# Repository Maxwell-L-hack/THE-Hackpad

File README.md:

# THE-hackpad
This macropad is a six key with the intention to have the basic game controls.

# Disassembled

# Overall Hackpad

# Schematic

# PCB

# BOM
## Seeed Studio RP2040
## LED_SK6812MINI_PLCC4_3.5x3.5mm_P1.75mm
## Cherry MX 1.00 u

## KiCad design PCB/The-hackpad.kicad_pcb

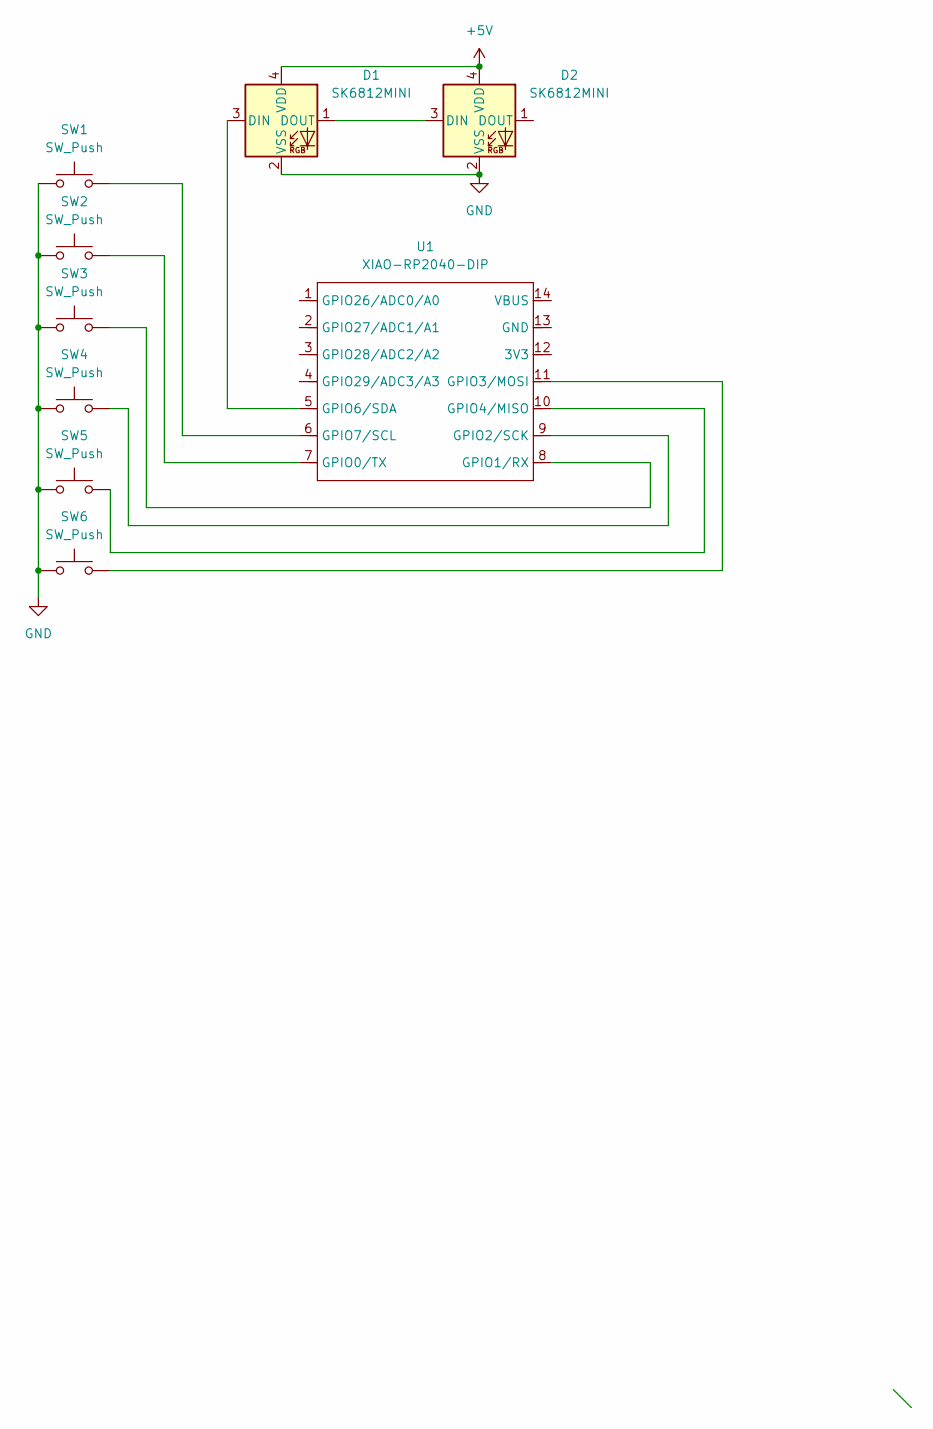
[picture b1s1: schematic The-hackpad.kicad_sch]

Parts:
D1, D2: SK6812MINI; LED_SK6812MINI_PLCC4_3.5x3.5mm_P1.75mm
SW1, SW2, SW3, SW4, SW5, SW6: SW_Push; SW_Cherry_MX_1.00u_PCB
U1: XIAO-RP2040-DIP

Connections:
+5V: D1.4 (VDD), D2.4 (VDD)
GND: D1.2 (VSS), D2.2 (VSS), SW1.1, SW2.1, SW3.1, SW4.1, SW5.1, SW6.1
unnamed: D1.3 (DIN), U1.5 (GPIO6/SDA)
unnamed: D1.1 (DOUT), D2.3 (DIN)
unnamed: SW2.2, U1.7 (GPIO0/TX)
unnamed: SW3.2, U1.8 (GPIO1/RX)
unnamed: SW4.2, U1.9 (GPIO2/SCK)
unnamed: SW6.2, U1.11 (GPIO3/MOSI)
unnamed: SW5.2, U1.10 (GPIO4/MISO)
unnamed: SW1.2, U1.6 (GPIO7/SCL)

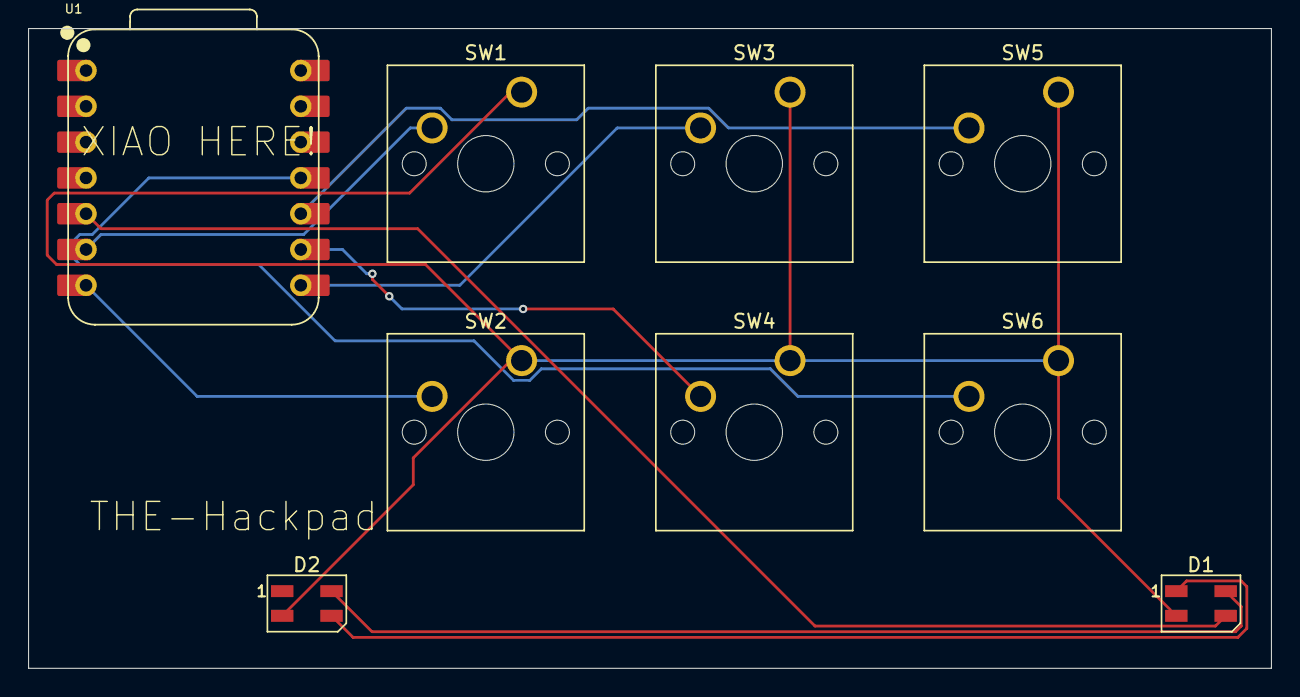
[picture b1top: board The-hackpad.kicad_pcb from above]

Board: 2 copper layers, 88.2 x 45.4 mm, 9 parts (0 on the bottom side), 10 nets.

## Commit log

2025-05-22 Started JOURNAL.md
2025-05-22 Added introductory sentence into README.md
2025-07-09 Added CAD files
2025-07-09 Added firmware files
2025-07-09 Added PCB files
2025-07-09 Added production files
2025-07-09 Added README
2025-07-10 Added BOM
2025-07-10 Removed the autosave and backup of the pcb
